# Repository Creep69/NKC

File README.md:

# NKC
## Neuauflage des NDR KLEIN COMPUTER

Hier sollen Hardware- und Softwareprojekte zum NDR Klein Computer ihren Platz finden.

Weitere Mitstreiter sind herzlich willkommen!

Links:

www.nkc-wiki.de

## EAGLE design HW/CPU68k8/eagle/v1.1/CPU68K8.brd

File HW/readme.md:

Platinenlayouts zur Neuauflage des NKC

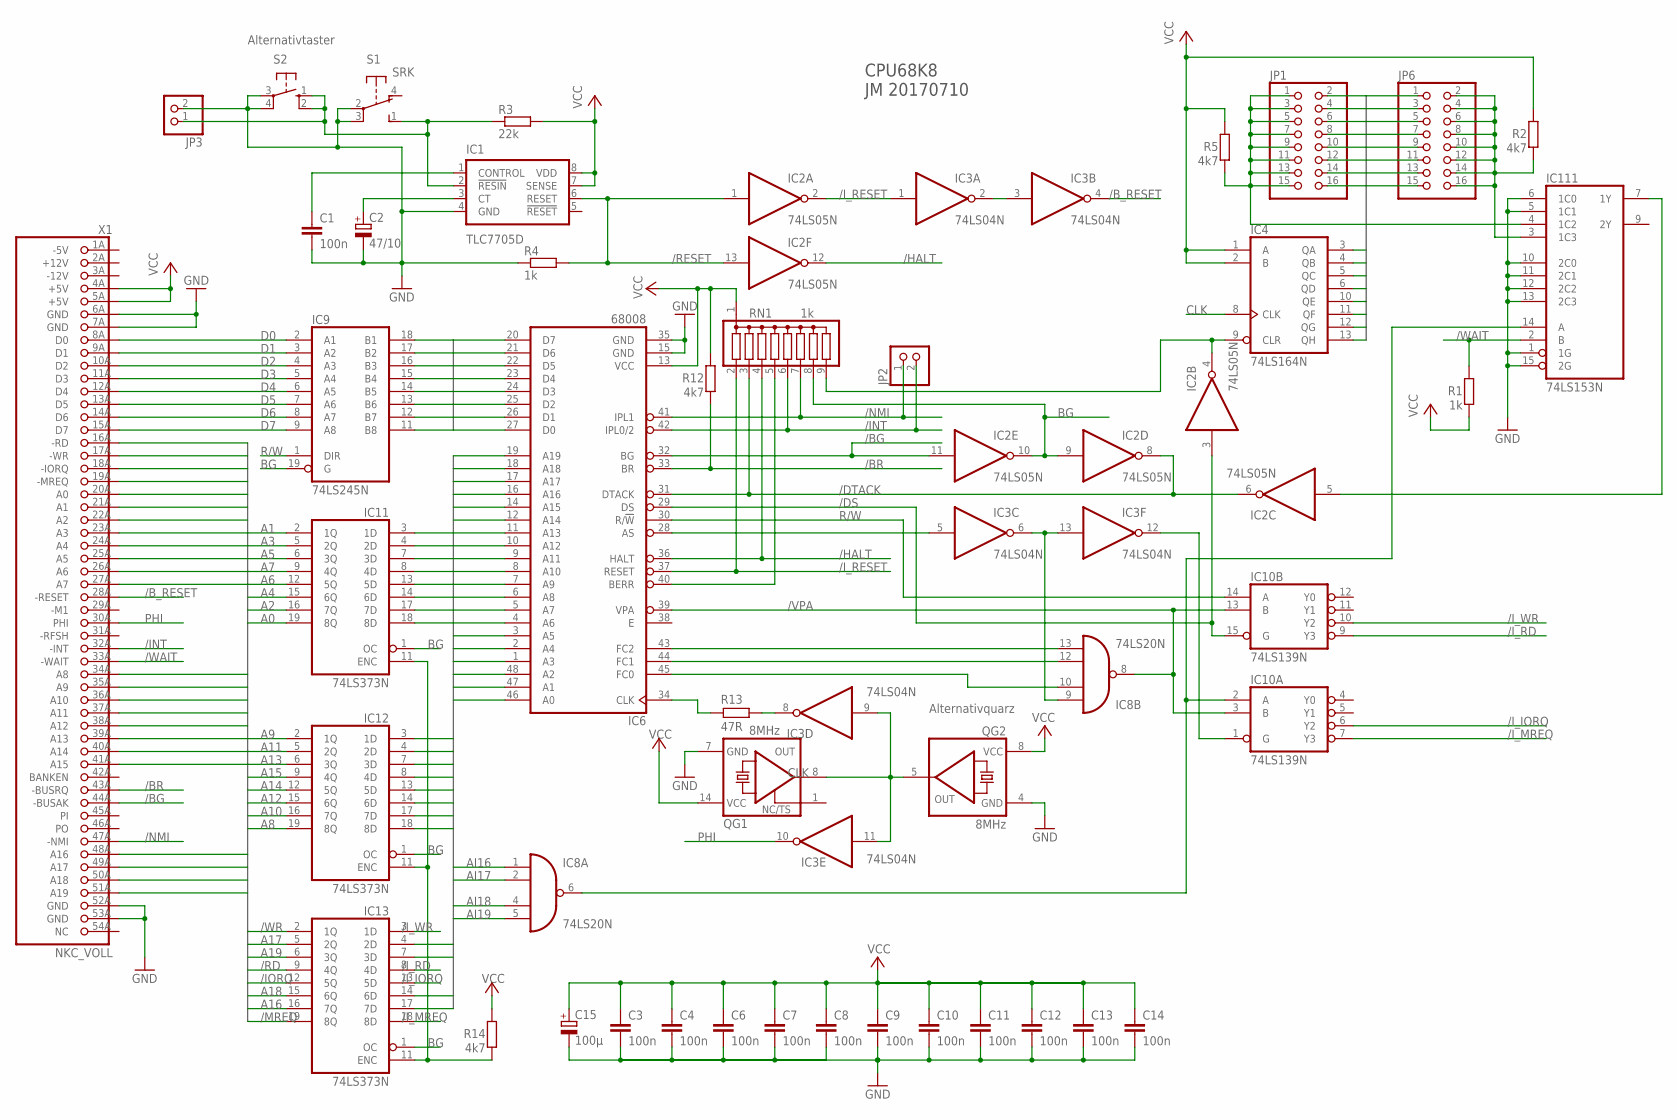
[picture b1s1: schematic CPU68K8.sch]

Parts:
C1, C3, C4, C6, C7, C8, C9, C10, C11, C12, C13, C14: 100n; C025-025X050
C2: 47/10; E2,5-6
C15: 100µ; E2,5-6
IC1: TLC7705D; DIL08
IC2: 74LS05N; DIL14
IC3: 74LS04N; DIL14
IC4: 74LS164N; DIL14
IC6: 68008; DIL48
IC8: 74LS20N; DIL14
IC9: 74LS245N; DIL20
IC10: 74LS139N; DIL16
IC11, IC12, IC13: 74LS373N; DIL20
IC111: 74LS153N; DIL16
JP1, JP6: PINHD-2X8; 2X08
JP2: PINHD-1X2; 1X02
JP3: PINHD-1X2/90; 1X02/90
QG1: 8MHz; DIL14S
QG2: 8MHz; DIL08S
R1, R4: 1k; 0207/10
R2, R5, R12, R14: 4k7; 0207/10
R3: 22k; 0207/10
R13: 47R; 0207/10
RN1: 1k; SIL9
S1: SRK
S2: 10-XX; B3F-10XX
X1: NKC_VOLL; 1X54/90_PCB

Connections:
+12V: X1.2A (+12V)
-5V: X1.1A (-5V)
-12V: X1.3A (-12V)
/BG: IC2.11 (I), IC6.32 (BG), X1.44A (-BUSAK)
/BR: IC6.33 (BR), R12.1, X1.43A (-BUSRQ)
/B_RESET: IC3.4 (O), X1.28A (-RESET)
/DS: IC2.3 (I), IC6.29 (DS), IC10.15 (G)
/DTACK: IC2.6 (O), IC2.8 (O), IC6.31 (DTACK), RN1.3
/HALT: IC2.12 (O), IC6.36 (HALT), RN1.4
/INT: IC6.42 (IPL0/2), JP2.2, RN1.6, X1.32A (-INT)
/IORQ: IC13.12 (5Q), X1.18A (-IORQ)
/I_IORQ: IC10.6 (Y2), IC13.13 (5D)
/I_MREQ: IC10.7 (Y3), IC13.18 (8D)
/I_RD: IC10.9 (Y3), IC13.8 (4D)
/I_RESET: IC2.2 (O), IC3.1 (I), IC6.37 (RESET), RN1.2
/I_WR: IC10.10 (Y2), IC13.3 (1D)
/MREQ: IC13.19 (8Q), X1.19A (-MREQ)
/NMI: IC6.41 (IPL1), JP2.1, RN1.7, X1.47A (-NMI)
/RD: IC13.9 (4Q), X1.16A (-RD)
/RESET: IC1.6 (RESET), IC2.1 (I), IC2.13 (I), R4.2
/VPA: IC6.39 (VPA), IC8.8 (O), IC10.3 (B), IC10.13 (B)
/WAIT: IC111.2 (B), R1.2, X1.33A (-WAIT)
/WR: IC13.2 (1Q), X1.17A (-WR)
A0: IC11.19 (8Q), X1.20A (A0)
A1: IC11.2 (1Q), X1.21A (A1)
A2: IC11.16 (7Q), X1.22A (A2)
A3: IC11.5 (2Q), X1.23A (A3)
A4: IC11.15 (6Q), X1.24A (A4)
A5: IC11.6 (3Q), X1.25A (A5)
A6: IC11.12 (5Q), X1.26A (A6)
A7: IC11.9 (4Q), X1.27A (A7)
A8: IC12.19 (8Q), X1.34A (A8)
A9: IC12.2 (1Q), X1.35A (A9)
A10: IC12.16 (7Q), X1.36A (A10)
A11: IC12.5 (2Q), X1.37A (A11)
A12: IC12.15 (6Q), X1.38A (A12)
A13: IC12.6 (3Q), X1.39A (A13)
A14: IC12.12 (5Q), X1.40A (A14)
A15: IC12.9 (4Q), X1.41A (A15)
A16: IC13.16 (7Q), X1.48A (A16)
A17: IC13.5 (2Q), X1.49A (A17)
A18: IC13.15 (6Q), X1.50A (A18)
A19: IC13.6 (3Q), X1.51A (A19)
AI0: IC6.46 (A0), IC11.18 (8D)
AI1: IC6.47 (A1), IC11.3 (1D)
AI2: IC6.48 (A2), IC11.17 (7D)
AI3: IC6.1 (A3), IC11.4 (2D)
AI4: IC6.2 (A4), IC11.14 (6D)
AI5: IC6.3 (A5), IC11.7 (3D)
AI6: IC6.4 (A6), IC11.13 (5D)
AI7: IC6.5 (A7), IC11.8 (4D)
AI8: IC6.6 (A8), IC12.18 (8D)
AI9: IC6.7 (A9), IC12.3 (1D)
AI10: IC6.8 (A10), IC12.17 (7D)
AI11: IC6.9 (A11), IC12.4 (2D)
AI12: IC6.10 (A12), IC12.14 (6D)
AI13: IC6.11 (A13), IC12.7 (3D)
AI14: IC6.12 (A14), IC12.13 (5D)
AI15: IC6.14 (A15), IC12.8 (4D)
AI16: IC6.16 (A16), IC8.1 (I0), IC13.17 (7D)
AI17: IC6.17 (A17), IC8.2 (I1), IC13.4 (2D)
AI18: IC6.18 (A18), IC8.4 (I2), IC13.14 (6D)
AI19: IC6.19 (A19), IC8.5 (I3), IC13.7 (3D)
BG: IC2.9 (I), IC2.10 (O), IC9.19 (G), IC11.1 (OC), IC12.1 (OC), IC13.1 (OC), RN1.8
CLK: IC3.9 (I), IC3.11 (I), IC4.8 (CLK), QG1.8 (OUT), QG2.5 (OUT)
D0: IC9.2 (A1), X1.8A (D0)
D1: IC9.3 (A2), X1.9A (D1)
D2: IC9.4 (A3), X1.10A (D2)
D3: IC9.5 (A4), X1.11A (D3)
D4: IC9.6 (A5), X1.12A (D4)
D5: IC9.7 (A6), X1.13A (D5)
D6: IC9.8 (A7), X1.14A (D6)
D7: IC9.9 (A8), X1.15A (D7)
DI0: IC6.27 (D0), IC9.18 (B1)
DI1: IC6.26 (D1), IC9.17 (B2)
DI2: IC6.25 (D2), IC9.16 (B3)
DI3: IC6.24 (D3), IC9.15 (B4)
DI4: IC6.23 (D4), IC9.14 (B5)
DI5: IC6.22 (D5), IC9.13 (B6)
DI6: IC6.21 (D6), IC9.12 (B7)
DI7: IC6.20 (D7), IC9.11 (B8)
GND: C1.2, C2.-, C3.2, C4.2, C6.2, C7.2, C8.2, C9.2, C10.2, C11.2, C12.2, C13.2, C14.2, C15.-, IC1.4 (GND), IC2.7 (GND), IC3.7 (GND), IC4.7 (GND), IC6.15 (GND), IC6.35 (GND), IC8.7 (GND), IC9.10 (GND), IC10.8 (GND), IC11.10 (GND), IC12.10 (GND), IC13.10 (GND), IC111.1 (1G), IC111.5 (1C1), IC111.6 (1C0), IC111.8 (GND), IC111.10 (2C0), IC111.11 (2C1), IC111.12 (2C2), IC111.13 (2C3), IC111.15 (2G), JP3.2, QG1.7 (GND), QG2.4 (GND), R4.1, S1.2, S1.3, S2.3, S2.4 (P1), X1.6A (GND), X1.7A (GND), X1.52A (GND), X1.53A (GND)
unnamed: IC6.43 (FC2), IC8.13 (I3)
unnamed: IC6.44 (FC1), IC8.12 (I2)
unnamed: IC6.45 (FC0), IC8.10 (I1)
unnamed: IC3.5 (I), IC6.28 (AS)
unnamed: IC3.6 (O), IC3.13 (I), IC8.9 (I0)
unnamed: IC6.34 (CLK), R13.2
unnamed: IC3.8 (O), R13.1
unnamed: IC2.4 (O), IC4.9 (CLR), RN1.9
unnamed: IC3.12 (O), IC10.1 (G)
unnamed: IC3.2 (O), IC3.3 (I)
unnamed: IC6.40 (BERR), RN1.5
unnamed: IC8.6 (O), IC10.2 (A), IC111.14 (A)
unnamed: IC2.5 (I), IC111.7 (1Y)
unnamed: IC11.11 (ENC), IC12.11 (ENC), IC13.11 (ENC), R14.1
unnamed: C1.1, IC1.1 (CONTROL)
unnamed: C2.+, IC1.3 (CT)
unnamed: IC111.4 (1C2), JP1.1, JP1.3, JP1.5, JP1.7, JP1.9, JP1.11, JP1.13, JP1.15, R5.1
unnamed: IC1.2 (!RESIN), JP3.1, R3.1, S1.1 (S), S2.1 (S), S2.2 (S1)
unnamed: IC111.3 (1C3), JP6.2, JP6.4, JP6.6, JP6.8, JP6.10, JP6.12, JP6.14, JP6.16, R2.1
PHI: IC3.10 (O), X1.30A (PHI)
R/W: IC6.30 (R/!W), IC9.1 (DIR), IC10.14 (A)
VCC: C3.1, C4.1, C6.1, C7.1, C8.1, C9.1, C10.1, C11.1, C12.1, C13.1, C14.1, C15.+, IC1.7 (SENSE), IC1.8 (VDD), IC2.14 (VCC), IC3.14 (VCC), IC4.1 (A), IC4.2 (B), IC4.14 (VCC), IC6.13 (VCC), IC8.14 (VCC), IC9.20 (VCC), IC10.16 (VCC), IC11.20 (VCC), IC12.20 (VCC), IC13.20 (VCC), IC111.16 (VCC), QG1.14 (VCC), QG2.8 (VCC), R1.1, R2.2, R3.2, R5.2, R12.2, R14.2, RN1.1, X1.4A (+5V), X1.5A (+5V)
WAIT1: IC4.3 (QA), JP1.2, JP6.1
WAIT2: IC4.4 (QB), JP1.4, JP6.3
WAIT3: IC4.5 (QC), JP1.6, JP6.5
WAIT4: IC4.6 (QD), JP1.8, JP6.7
WAIT5: IC4.10 (QE), JP1.10, JP6.9
WAIT6: IC4.11 (QF), JP1.12, JP6.11
WAIT7: IC4.12 (QG), JP1.14, JP6.13
WAIT8: IC4.13 (QH), JP1.16, JP6.15

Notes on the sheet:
CPU68K8 JM 20170710
Alternativquarz
Alternativtaster

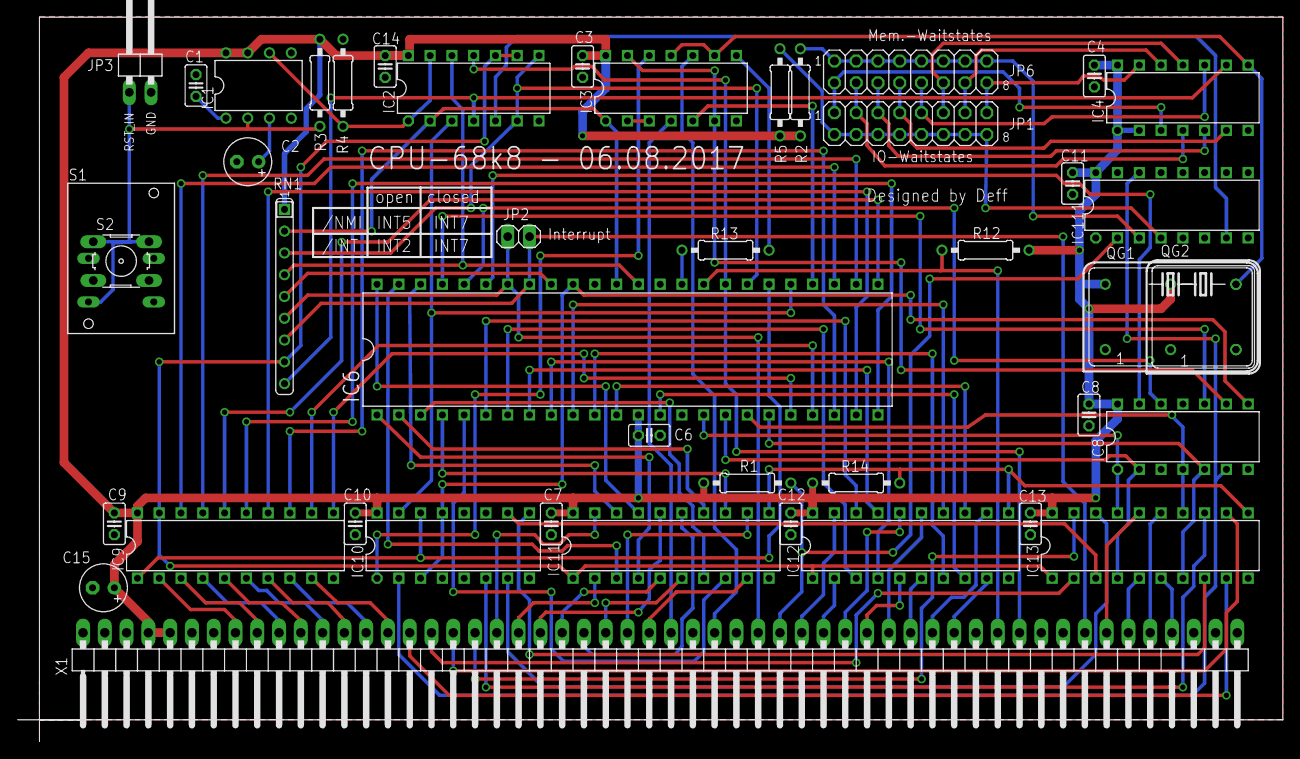
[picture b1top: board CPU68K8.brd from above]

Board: 2 copper layers, 147.5 x 84.4 mm, 44 parts (0 on the bottom side), 109 nets.

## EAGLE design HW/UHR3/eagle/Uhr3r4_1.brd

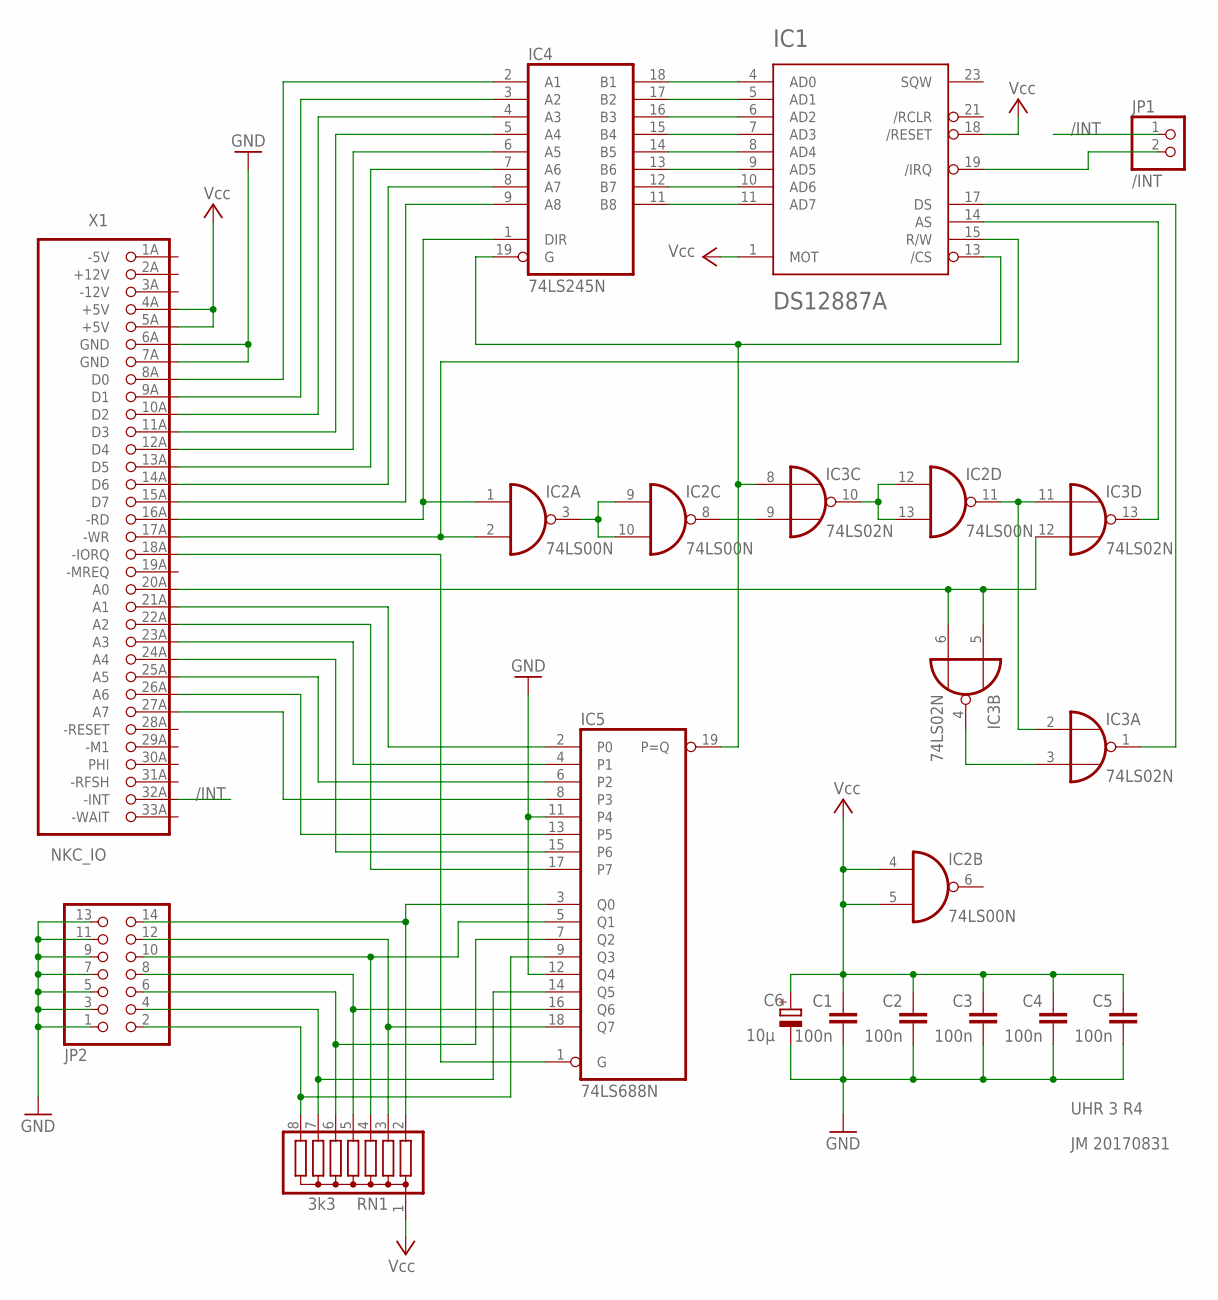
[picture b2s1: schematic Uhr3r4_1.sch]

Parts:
C1, C2, C3, C4, C5: 100n; C025-025X050
C6: 10µ; E2,5-5
IC1: DS12887A; DIL24-6_DS
IC2: 74LS00N; DIL14
IC3: 74LS02N; DIL14
IC4: 74LS245N; DIL20
IC5: 74LS688N; DIL20
JP1: /INT; 1X02
JP2: PINHD-2X7; 2X07
RN1: 3k3; SIL8
X1: NKC_IO; 1X33/90_PCB

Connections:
+12V: X1.2A (+12V)
-5V: X1.1A (-5V)
-12V: X1.3A (-12V)
/INT: JP1.1, X1.32A (-INT)
GND: C1.1, C2.1, C3.1, C4.1, C5.1, C6.-, IC1.12 (GND), IC2.7 (GND), IC3.7 (GND), IC4.10 (GND), IC5.10 (GND), IC5.11 (P4), IC5.12 (Q4), JP2.1, JP2.3, JP2.5, JP2.7, JP2.9, JP2.11, JP2.13, X1.6A (GND), X1.7A (GND)
unnamed: IC4.2 (A1), X1.8A (D0)
unnamed: IC4.3 (A2), X1.9A (D1)
unnamed: IC4.4 (A3), X1.10A (D2)
unnamed: IC4.5 (A4), X1.11A (D3)
unnamed: IC4.6 (A5), X1.12A (D4)
unnamed: IC4.7 (A6), X1.13A (D5)
unnamed: IC4.8 (A7), X1.14A (D6)
unnamed: IC4.9 (A8), X1.15A (D7)
unnamed: IC1.4 (AD0), IC4.18 (B1)
unnamed: IC1.5 (AD1), IC4.17 (B2)
unnamed: IC1.6 (AD2), IC4.16 (B3)
unnamed: IC1.7 (AD3), IC4.15 (B4)
unnamed: IC1.8 (AD4), IC4.14 (B5)
unnamed: IC1.9 (AD5), IC4.13 (B6)
unnamed: IC1.10 (AD6), IC4.12 (B7)
unnamed: IC1.11 (AD7), IC4.11 (B8)
unnamed: IC1.15 (R/W), IC2.2 (I1), X1.17A (-WR)
unnamed: IC5.3 (Q0), JP2.14, RN1.2
unnamed: IC5.18 (Q7), JP2.12, RN1.3
unnamed: IC5.5 (Q1), JP2.10, RN1.4
unnamed: IC5.16 (Q6), JP2.8, RN1.5
unnamed: IC5.7 (Q2), JP2.6, RN1.6
unnamed: IC5.14 (Q5), JP2.4, RN1.7
unnamed: IC5.9 (Q3), JP2.2, RN1.8
unnamed: IC5.2 (P0), X1.21A (A1)
unnamed: IC5.17 (P7), X1.22A (A2)
unnamed: IC5.4 (P1), X1.23A (A3)
unnamed: IC5.15 (P6), X1.24A (A4)
unnamed: IC5.6 (P2), X1.25A (A5)
unnamed: IC5.13 (P5), X1.26A (A6)
unnamed: IC5.8 (P3), X1.27A (A7)
unnamed: IC2.1 (I0), IC4.1 (DIR), X1.16A (-RD)
unnamed: IC1.19 (/IRQ), JP1.2
unnamed: IC2.3 (O), IC2.9 (I0), IC2.10 (I1)
unnamed: IC2.8 (O), IC3.9 (I1)
unnamed: IC1.13 (/CS), IC3.8 (I0), IC4.19 (G), IC5.19 (P=Q)
unnamed: IC2.12 (I0), IC2.13 (I1), IC3.10 (O)
unnamed: IC3.5 (I0), IC3.6 (I1), IC3.12 (I1), X1.20A (A0)
unnamed: IC2.11 (O), IC3.2 (I0), IC3.11 (I0)
unnamed: IC3.3 (I1), IC3.4 (O)
unnamed: IC1.14 (AS), IC3.13 (O)
unnamed: IC1.17 (DS), IC3.1 (O)
unnamed: IC5.1 (G), X1.18A (-IORQ)
VCC: C1.2, C2.2, C3.2, C4.2, C5.2, C6.+, IC1.1 (MOT), IC1.18 (/RESET), IC1.24 (VCC), IC2.4 (I0), IC2.5 (I1), IC2.14 (VCC), IC3.14 (VCC), IC4.20 (VCC), IC5.20 (VCC), RN1.1, X1.4A (+5V), X1.5A (+5V)

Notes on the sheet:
JM 20170831
UHR 3 R4

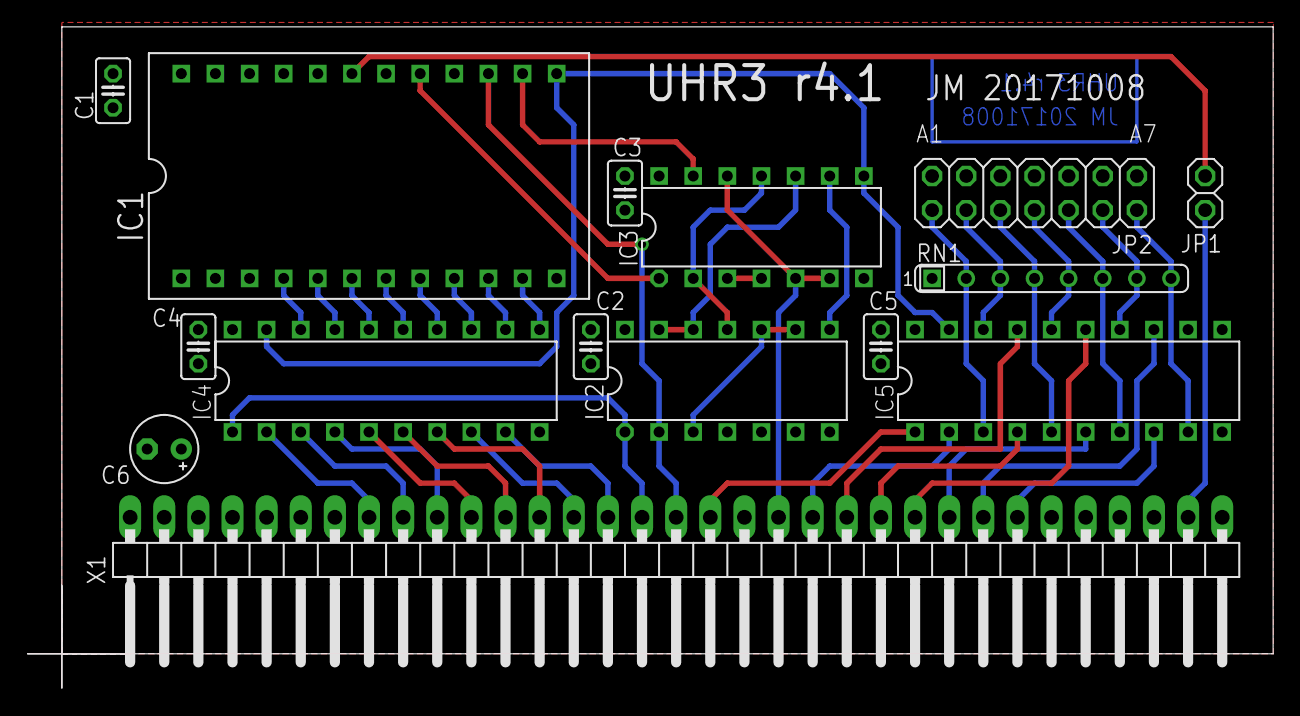
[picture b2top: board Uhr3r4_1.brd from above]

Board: 2 copper layers, 92.6 x 49.1 mm, 15 parts (0 on the bottom side), 46 nets.

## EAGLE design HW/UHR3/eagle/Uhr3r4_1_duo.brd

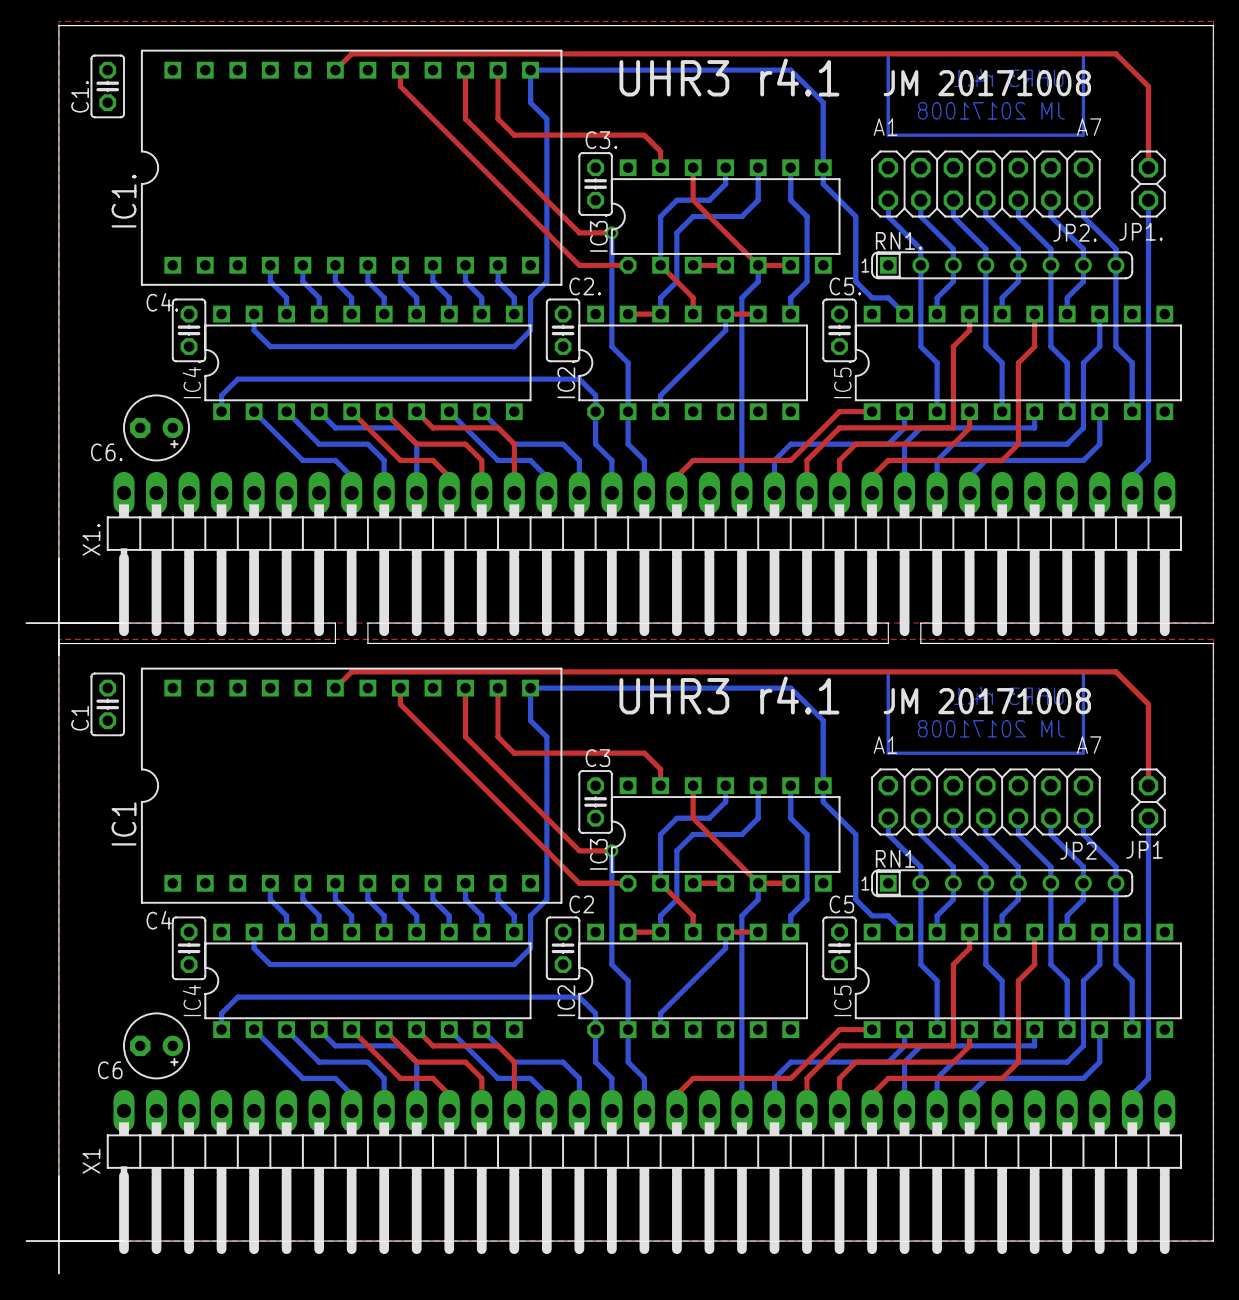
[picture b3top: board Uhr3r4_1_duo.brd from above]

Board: 2 copper layers, 92.6 x 97.4 mm, 30 parts (0 on the bottom side), 92 nets.

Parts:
C1, C1., C2, C2., C3, C3., C4, C4., C5, C5.: 100n; C025-025X050
C6, C6.: 10µ; E2,5-5
IC1, IC1.: DS12887A; DIL24-6_DS
IC2, IC2.: 74LS00N; DIL14
IC3, IC3.: 74LS02N; DIL14
IC4, IC4.: 74LS245N; DIL20
IC5, IC5.: 74LS688N; DIL20
JP1, JP1.: /INT; 1X02
JP2, JP2.: 2X07
RN1, RN1.: 3k3; SIL8
X1, X1.: NKC_IO; 1X33/90_PCB

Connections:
/INT: JP1.1, X1.32A
/INT1: JP1..1, X1..32A
GND: C1.1, C2.1, C3.1, C4.1, C5.1, C6.-, IC1.12, IC2.7, IC3.7, IC4.10, IC5.10, IC5.11, IC5.12, JP2.1, JP2.3, JP2.5, JP2.7, JP2.9, JP2.11, JP2.13, X1.6A, X1.7A
GND1: C1..1, C2..1, C3..1, C4..1, C5..1, C6..-, IC1..12, IC2..7, IC3..7, IC4..10, IC5..10, IC5..11, IC5..12, JP2..1, JP2..3, JP2..5, JP2..7, JP2..9, JP2..11, JP2..13, X1..6A, X1..7A
unnamed: IC4.2, X1.8A
unnamed: IC4.3, X1.9A
unnamed: IC4.4, X1.10A
unnamed: IC4.5, X1.11A
unnamed: IC4.6, X1.12A
unnamed: IC4.7, X1.13A
unnamed: IC4.8, X1.14A
unnamed: IC4.9, X1.15A
unnamed: IC1.4, IC4.18
unnamed: IC1.5, IC4.17
unnamed: IC1.6, IC4.16
unnamed: IC1.7, IC4.15
unnamed: IC1.8, IC4.14
unnamed: IC1.9, IC4.13
unnamed: IC1.10, IC4.12
unnamed: IC1.11, IC4.11
unnamed: IC1.15, IC2.2, X1.17A
unnamed: IC5.3, JP2.14, RN1.2
unnamed: IC5.18, JP2.12, RN1.3
unnamed: IC5.5, JP2.10, RN1.4
unnamed: IC5.16, JP2.8, RN1.5
unnamed: IC5.7, JP2.6, RN1.6
unnamed: IC5.14, JP2.4, RN1.7
unnamed: IC5.9, JP2.2, RN1.8
unnamed: IC5.2, X1.21A
unnamed: IC5.17, X1.22A
unnamed: IC5.4, X1.23A
unnamed: IC5.15, X1.24A
unnamed: IC5.6, X1.25A
unnamed: IC5.13, X1.26A
unnamed: IC5.8, X1.27A
unnamed: IC2.1, IC4.1, X1.16A
unnamed: IC1.19, JP1.2
unnamed: IC2.3, IC2.9, IC2.10
unnamed: IC2.8, IC3.9
unnamed: IC1.13, IC3.8, IC4.19, IC5.19
unnamed: IC2.12, IC2.13, IC3.10
unnamed: IC3.5, IC3.6, IC3.12, X1.20A
unnamed: IC2.11, IC3.2, IC3.11
unnamed: IC3.3, IC3.4
unnamed: IC1.14, IC3.13
unnamed: IC1.17, IC3.1
unnamed: IC4..2, X1..8A
unnamed: IC5.1, X1.18A
unnamed: IC4..3, X1..9A
unnamed: IC4..4, X1..10A
unnamed: IC4..5, X1..11A
unnamed: IC4..6, X1..12A
unnamed: IC4..7, X1..13A
unnamed: IC4..8, X1..14A
unnamed: IC4..9, X1..15A
unnamed: IC1..4, IC4..18
unnamed: IC1..5, IC4..17
unnamed: IC1..6, IC4..16
unnamed: IC1..7, IC4..15
unnamed: IC1..8, IC4..14
unnamed: IC1..9, IC4..13
unnamed: IC1..10, IC4..12
unnamed: IC1..11, IC4..11
unnamed: IC5..3, JP2..14, RN1..2
unnamed: IC5..5, JP2..10, RN1..4
unnamed: IC5..16, JP2..8, RN1..5
unnamed: IC5..7, JP2..6, RN1..6
unnamed: IC5..14, JP2..4, RN1..7
unnamed: IC5..9, JP2..2, RN1..8
unnamed: IC5..2, X1..21A
unnamed: IC5..17, X1..22A
unnamed: IC5..4, X1..23A
unnamed: IC5..15, X1..24A
unnamed: IC5..6, X1..25A
unnamed: IC5..13, X1..26A
unnamed: IC5..8, X1..27A
unnamed: IC1..15, IC2..2, X1..17A
unnamed: IC2..1, IC4..1, X1..16A
unnamed: IC2..3, IC2..9, IC2..10
unnamed: IC2..8, IC3..9
unnamed: IC1..13, IC3..8, IC4..19, IC5..19
unnamed: IC2..12, IC2..13, IC3..10
unnamed: IC3..5, IC3..6, IC3..12, X1..20A
unnamed: IC2..11, IC3..2, IC3..11
unnamed: IC3..3, IC3..4
unnamed: IC1..14, IC3..13
unnamed: IC1..17, IC3..1
unnamed: IC5..1, X1..18A
unnamed: IC5..18, JP2..12, RN1..3
unnamed: IC1..19, JP1..2
VCC: C1.2, C2.2, C3.2, C4.2, C5.2, C6.+, IC1.1, IC1.18, IC1.24, IC2.4, IC2.5, IC2.14, IC3.14, IC4.20, IC5.20, RN1.1, X1.4A, X1.5A
VCC1: C1..2, C2..2, C3..2, C4..2, C5..2, C6..+, IC1..1, IC1..18, IC1..24, IC2..4, IC2..5, IC2..14, IC3..14, IC4..20, IC5..20, RN1..1, X1..4A, X1..5A

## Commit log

2017-10-20 Create NKC-BUS2
2017-10-20 Create sprint_layout_6
2017-10-20 Version v1.2 und v1.2 der BUS2 Platine für Sprint Layout 6
2017-10-20 Gerber Files der v1.2 der BUS2 Platine Passend für z.B. Elecrow und DirtyPCB
2017-10-20 change in structure
2017-10-20 initial
2017-10-20 initial release
2017-10-20 initial version
2017-12-03 Dokumentation für CSP Platine
2018-02-04 Dokumentation zur IO-USB
2019-01-03 Version 0.1 Prototyp
2019-01-26 Zusätzliche Verbindung für Tastaturpuffer.
2021-06-12 initial version of python_dl
2021-06-13 added Macro for SER Overflow check
2021-06-13 added DS utility
2021-06-13 added readme
2021-06-15 update and cleanup
2021-06-15 initial version of xtree
2021-06-15 Small update
2021-06-15 Minor update
2021-06-16 initial version of XDIR
2021-06-16 move files to 68k folder
2021-06-16 update Python to take care on file end of ascii files
2021-06-16 initial version of color-mandelbrot
2021-06-19 Unterverzeichnisse fuer Programmiersprachen Erstes "Hello World" Programm in C
2021-06-19 erste Routinen zur Nutzung der CAS-neo in C Programmen
2021-06-19 minor cleanup
2021-06-19 Update typo
2021-06-30 Bugfix for HDD's
2021-07-01 bugfix for HDD's and copy command
2021-07-05 added xt.68k
2021-07-11 bugfix for send_file
2021-07-18 Erster Testcode fuer NKC-LCD
2021-07-20 added executable for 68008 and 68000
2021-07-27 Added 68k exe for 68008 + 68000
2021-07-30 small bugfix
2021-08-04 Testroutine fuer SOUND3 auf 0x50
2021-08-30 Update - added 115200 Baud for GDP-FPGA
2021-10-16 add CPU68k8 layout files
2021-10-16 add CPU68k16 layout files
2021-10-16 add BANKBOOT2 layout files
2021-10-16 add BWS layout files
2021-10-16 add CPU8080 layout files
2021-10-16 add GDP64HS layout files
2021-10-16 add updated NKC-LCD gerber files
2021-10-16 add updated SOUND3 layout files
2021-10-16 add updated SIO-CTC-PIO layout files
2022-09-24 initial Version of Tetris Game for NKC
2022-09-29 Update for tetris
2022-10-09 update - Save of Highscore
2022-10-10 bugfix for highscore list and stone rotation
2023-01-07 minor bugfix
2023-01-17 new version now with beginner and intermediate (commandline parameter: -i) mode and 3D effects
2023-10-22 added mine_m (S/W output) for regular GDP64-HS
2023-10-22 Added keyboard mode
2023-10-29 update for S/W Version of Minesweeper - stores now also highscore to file. May be displayed when started with -h Parameter
2023-10-30 update added explosion sound
2023-10-31 bugfix
2024-03-29 Update sysinfo.asm
    Ein paar Zeilen, um beim SCSI-Laufwerk Namen und Modell anzuzeigen statt nur "vorhanden". GitHub will leider immer die Umlaute in UTF-8 ändern, müssen wir mal sehen, ob das klappt.
2024-04-05 Update sysinfo.asm
    Wert von gets2i in D2 statt D1 retten, da der folgende SCSI-Befehl D1 überschreibt.
2025-10-15 Ansicht der BUS2
    BUS2 Neuauflage 26.4.2017 v1.2 RV mit Platinenhalterung und 5V Anschlusskabel via Anderson Powerpoles
2025-10-15 Create 20251014_BUS2.txt
    Kurze Beschreibung zur Konfektionierung der BUS2
2025-10-15 STL Datei für Platinenhalter zu BUS2
    STL Datei zum Ausdruck des Platinenhalters für die NKC BUS2 (Neuauflage 26.4.2017 v 1.2 RV) auf dem 3D-Drucker
2025-10-20 Readme.md
2025-10-21 Update Info zur BUs2
2025-10-21 Datei umbenannt
2025-10-21 Bauinformation
